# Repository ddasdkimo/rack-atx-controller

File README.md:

# Rack ATX Controller · B.2 / R.3

十台 Linux 主機共用一塊 POWER／RESET 遠端按鍵控制板。**100×110 mm、兩層的 R.3 佈線版已連通；中央板與轉接板 DRC／未連接均為 0。尚未製造放行。**

[公開佈局](https://rack-atx-controller-ddasdkimo.raidavid.chatgpt.site/layout.html) · [3D／兩台主機接線](https://rack-atx-controller-ddasdkimo.raidavid.chatgpt.site/) · [BOM](https://rack-atx-controller-ddasdkimo.raidavid.chatgpt.site/bom.html)

## 本版變更

- R.3 完成 USB 主對、Ethernet 終端集中、QFN 熱孔／鋼網窗，CC 電阻移近接頭。8 個 Ethernet 零件改為相同額定值的 0402；新增一個 Extended 料號，裝料費每單約多 US$3.07。原電路功能、接頭與 GPIO 不變。

- 移除全部 LED 偵測及十組隔離電源，保留二十個 TLP3122A 雙向隔離接點。原 POWER／RESET 按鈕經被動分接板並聯；原機殼 LED 直接留在主機板上。
- 原理圖／BOM 為 B.2；R.3 原生 PCB 有 300 個電氣元件、4 個固定孔、3,855 段走線與 252 個過孔。較 S.2 的 200×170 mm 面積減少約 68%。
- 修正模擬發現的計時與開機預設電位問題：MC14541B 計數式限時、1 nF C0G、獨立 ARM 閘控，GPIO 改為 4／6／7。
- 兩板 ERC／DRC／未連接均為 0。26×34 mm 被動轉接板為 6 個元件、30 段走線。16 組角落與 9 種狀態的 ngspice 行為模型通過，模型脈寬 11.26–21.46 秒。USB／Ethernet 的原生幾何與回流已由指定 CLI 獨立複查；兩層板沒有工廠控阻保證，尚未完成實板資格驗證，還需工廠 DFM 和實機驗證；目前已有 Gerber／鑽孔／BOM／CPL 審閱包，第二輪獨立離線加工檔複查沒有發現阻擋項；已取得五片完整報價；JLC 校正數值已通過獨立複查；TVS／網路座的供應商方向及 QFN 工藝仍待客服確認，尚未製造放行。

## 設計檔

- [B.2 KiCad 原理圖與 R.3 PCB](hardware/cad/B2/)
- [主控原理圖 PDF](hardware/release/controller-schematic.pdf)／[被動分接板 PDF](hardware/release/adapter-schematic.pdf)
- [硬體與接線](hardware/HARDWARE.md)／[佈局理由](hardware/LAYOUT-S3.md)／[R.3 佈線檢查與限制](hardware/ROUTING-R3.md)
- [BOM 與成本](hardware/bom/)／[費率假設](hardware/JLCPCB.md)
- [模擬方法與限制](hardware/simulation/README.md)／[B.2 結果](hardware/simulation/results/B2-summary.json)

J01–J10 是自訂 JST PHD 10 pin，**不是主機板通用 F_PANEL 或 Ethernet**。只接 pin 1/2 POWER、3/4 RESET、9 本機按鍵 ESD 參考地；5–8、10 不接。每台 HOST_REF 僅屬該台，與主控及其他主機保持隔離。線束與主機板跳線按實際手冊逐台核對。

## 成本範圍

2026-10-15 在登入 JLC 後取得五片正常 Economic 報價：**裸板 US$28.25、零件 US$168.86、組裝相關費 US$78.37，合計 US$275.48**，平均 US$55.10／片。板子＋零件為 US$197.11。採 ENIG 1µin／蓋油，一般交期、不加急；未含運稅、轉接板、線束、外殼與供電配件。QFN 工藝及 CPL 校正仍待確認，不代表已可生產。詳見 [實際報價](hardware/JLCPCB.md) 及 [加工檔審閱包](hardware/manufacturing/R3-candidate)。

## 重建

```sh
python3 scripts/build.py
python3 scripts/check.py
python3 -m http.server 8766 --directory dist
```

電路與原生 PCB 的完整重建方式見 [CAD 說明](hardware/cad/README.md)。3D 使用固定版本 Three.js，元件本體為簡化外形，但中央板與轉接板尺寸／位置／銅箔來自原生 KiCad；兩台主機為接線示意。網站沒有操作真實主機或上傳私密資訊的功能。

每次硬體變動須同步原理圖、BOM、3D、接線圖與公開網頁，見 [AGENTS.md](AGENTS.md)。B.1／S.2／R.0／R.1 資料與本機走線檢查點保留為歷史，不能繼續當作現行電路。

送件進度與證據見 [檢查清單](hardware/RELEASE-CHECKLIST.md)。客服問題結案後固定最終送樣包，再請同一位 `rack-atx-controller` 複查。

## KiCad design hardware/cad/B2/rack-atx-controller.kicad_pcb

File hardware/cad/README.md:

# Active CAD: B.2 schematic / R.2 routing

Open `B2/rack-atx-controller.kicad_pro` for the controller schematic; `B2/adapter.kicad_pro` for the six-component passive adapter; `B2/rack-atx-controller.kicad_pcb` in PCB Editor for the 100×110 mm routed candidate. Routing was authorized by the user. No Gerber or CPL exists.

The B.2 controller contains 300 electrical components; the placement adds four M3 holes. The controller has 2,754 track segments and 185 vias; the 26×34 mm adapter has 30 segments and no vias. Both boards have zero native unconnected items and configured DRC violations. The web 3D uses native placement, copper and adapter coordinates with simplified component envelopes. USB/Ethernet qualification, factory DFM and physical tests remain; see ../ROUTING-R2.md. Generators write into B2/placement to preserve the routed master.

```sh
python3 scripts/make-schematic.py
kicad-cli sch export netlist --format kicadxml -o artifacts/local/controller.xml hardware/cad/B2/rack-atx-controller.kicad_sch
kicad-cli sch export netlist --format kicadxml -o artifacts/local/adapter.xml hardware/cad/B2/adapter.kicad_sch
kicad-cli sch erc --format json -o artifacts/local/erc.json hardware/cad/B2/rack-atx-controller.kicad_sch
kicad-cli sch erc --format json -o artifacts/local/adapter-erc.json hardware/cad/B2/adapter.kicad_sch
python3 scripts/check-circuit.py
python3 hardware/simulation/run-b2.py
python3 scripts/cost.py
kicad-cli sch export pdf -o hardware/release/controller-schematic.pdf hardware/cad/B2/rack-atx-controller.kicad_sch
kicad-cli sch export pdf -o hardware/release/adapter-schematic.pdf hardware/cad/B2/adapter.kicad_sch
```

Run from the repository root. Use KiCad's bundled Python (wx + pcbnew) for `scripts/make-layout-s3.py` and `scripts/check-layout-s3.py`, then `kicad-cli pcb drc --format json -o artifacts/local/s3-drc.json hardware/cad/B2/rack-atx-controller.kicad_pcb`. Export/ ERC operations on the same project must run sequentially. Source library paths in generators currently target macOS KiCad; adapt paths on other platforms.

BOM, schematic and PCB candidate footprints agree; custom TLP3122A and input-terminal land patterns live in `RackATX.pretty`, referenced relative to B2. Manufacturer/physical DFM qualification is still required. Raw CLI netlists stay ignored because they include workstation paths. Never publish them. Historical CAD in this directory and archive/B1 is retained, not the current revision.

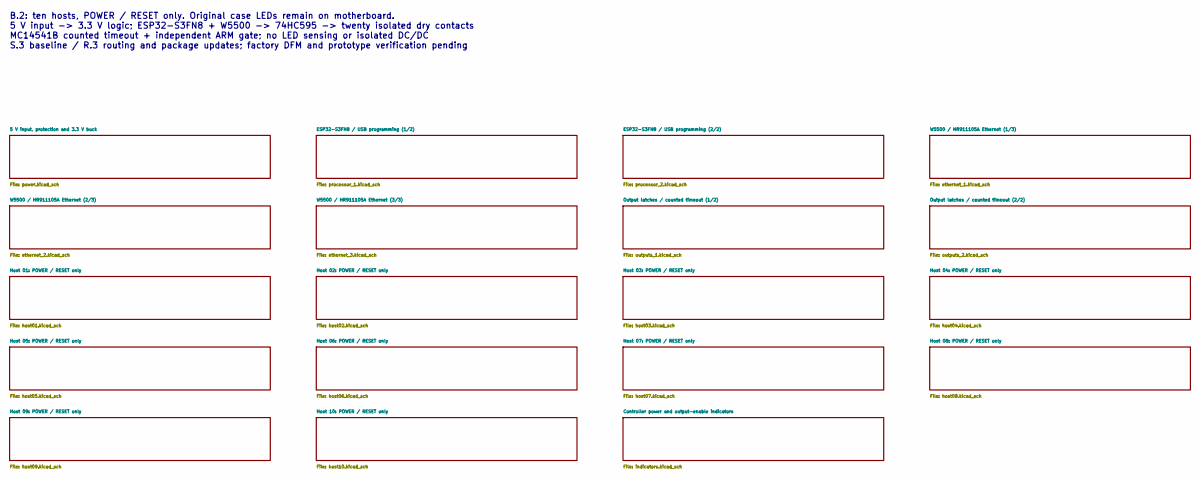
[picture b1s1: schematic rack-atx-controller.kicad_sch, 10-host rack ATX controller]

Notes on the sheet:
B.2: ten hosts, POWER / RESET only. Original case LEDs remain on motherboard. 5 V input -> 3.3 V logic; ESP32-S3FN8 + W5500 -> 74HC595 -> twenty isolated dry contacts MC14541B counted timeout + independent ARM gate; no LED sensing or isolated DC/DC S.3 baseline / R.3 routing and package updates; fa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

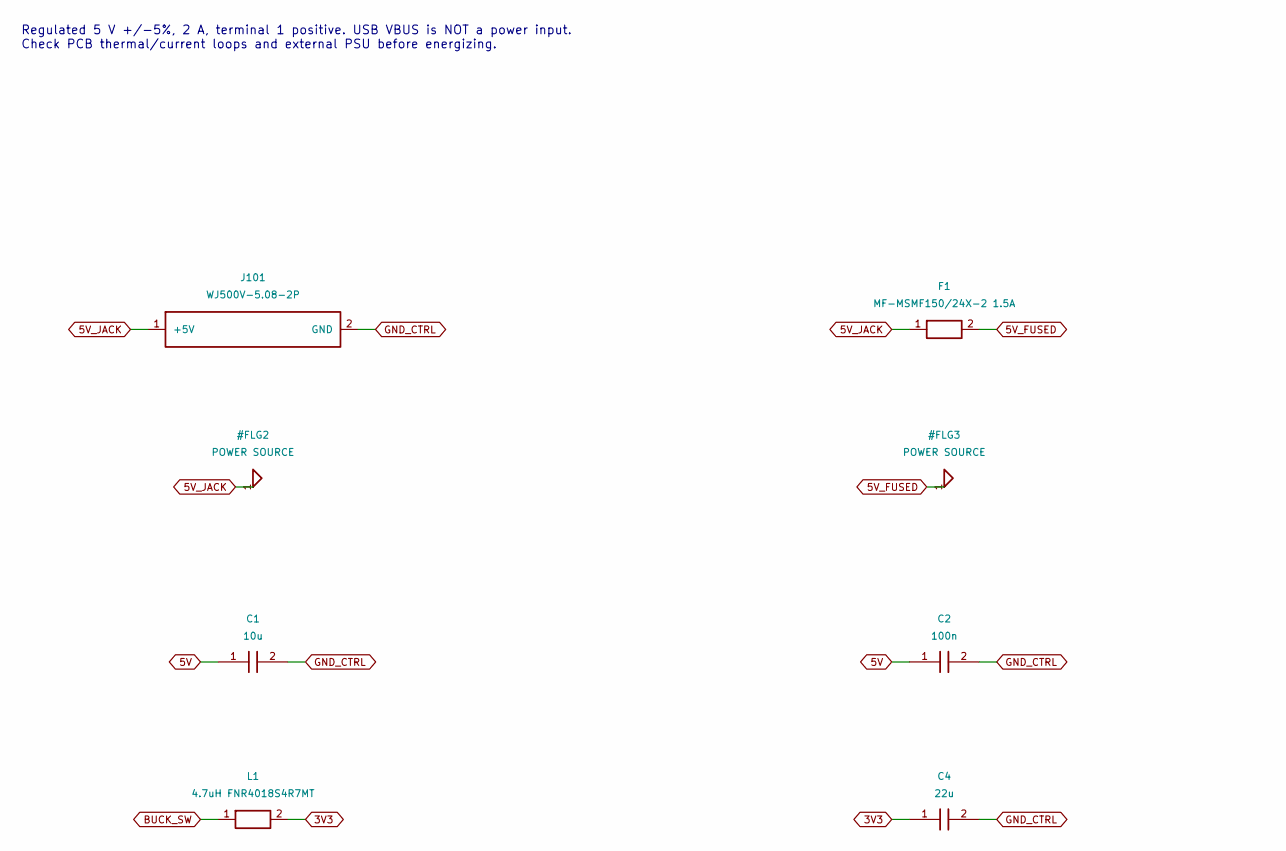
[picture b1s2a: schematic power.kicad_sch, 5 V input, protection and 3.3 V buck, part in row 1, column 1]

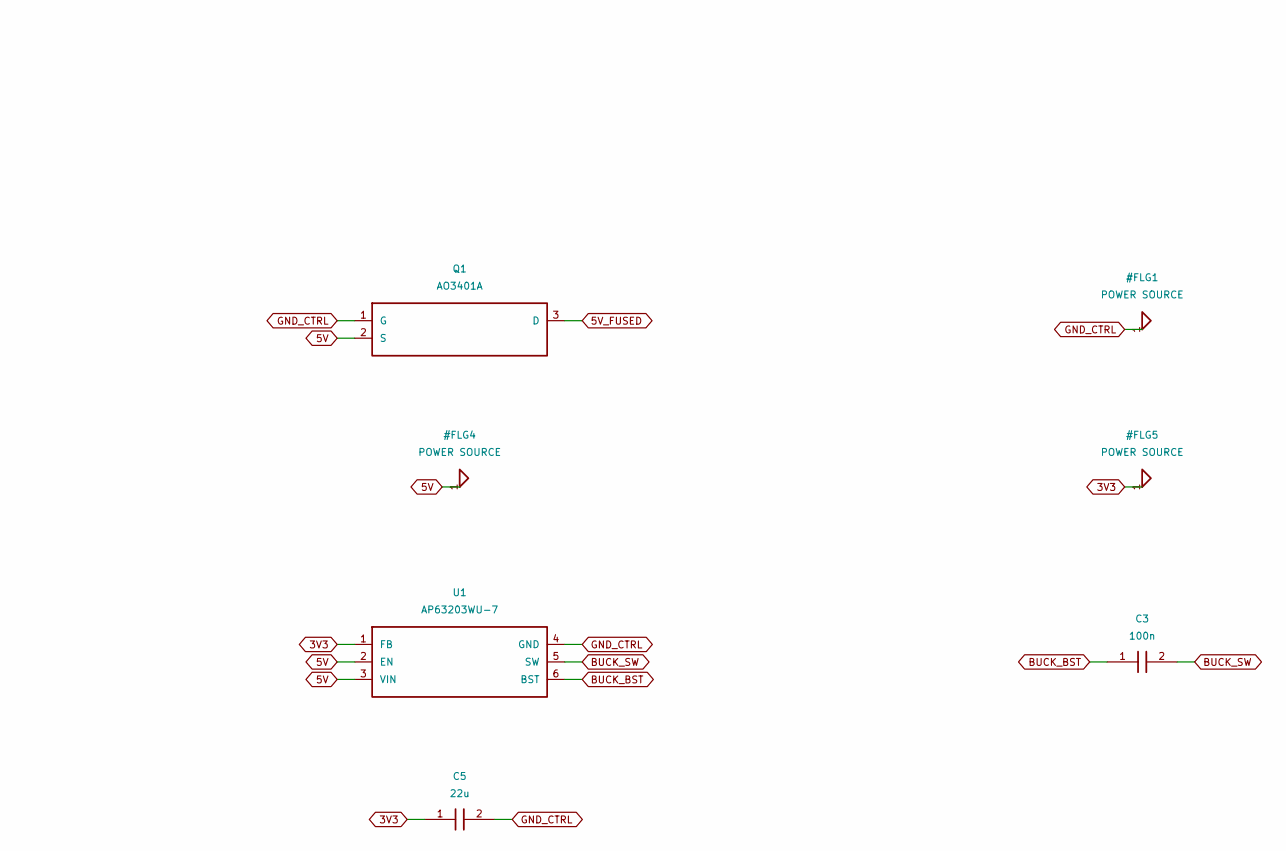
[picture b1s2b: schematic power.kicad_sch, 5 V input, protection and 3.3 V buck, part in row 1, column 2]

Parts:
C1: 10u; C_0805_2012Metric; MPN CL21A106KAYNNNE; LCSC C15850
C2, C3: 100n; C_0603_1608Metric; MPN CC0603KRX7R9BB104; LCSC C14663
C4, C5: 22u; C_0805_2012Metric; MPN CL21A226MAQNNNE; LCSC C45783
F1: MF-MSMF150/24X-2 1.5A; Fuse_1812_4532Metric; MPN MF-MSMF150/24X-2; LCSC C78695
J101: WJ500V-5.08-2P; WJ500V_5.08_2P; MPN WJ500V-5.08-2P; LCSC C8465
L1: 4.7uH FNR4018S4R7MT; L_Changjiang_FNR4018S; MPN FNR4018S4R7MT; LCSC C167806
Q1: AO3401A; SOT-23; MPN AO3401A; LCSC C15127
U1: AP63203WU-7; TSOT-23-6; MPN AP63203WU-7; LCSC C780769

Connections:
3V3: C4.1, C5.1, L1.2, U1.1 (FB); also elsewhere on the board
5V: C1.1, C2.1, Q1.2 (S), U1.2 (EN), U1.3 (VIN); also elsewhere on the board
5V_FUSED: F1.2, Q1.3 (D)
5V_JACK: F1.1, J101.1 (+5V)
BUCK_BST: C3.1, U1.6 (BST)
BUCK_SW: C3.2, L1.1, U1.5 (SW)
GND_CTRL: C1.2, C2.2, C4.2, C5.2, J101.2 (GND), Q1.1 (G), U1.4 (GND); also elsewhere on the board

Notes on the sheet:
Regulated 5 V +/-5%, 2 A, terminal 1 positive. USB VBUS is NOT a power input. Check PCB thermal/current loops and external PSU before energizing.

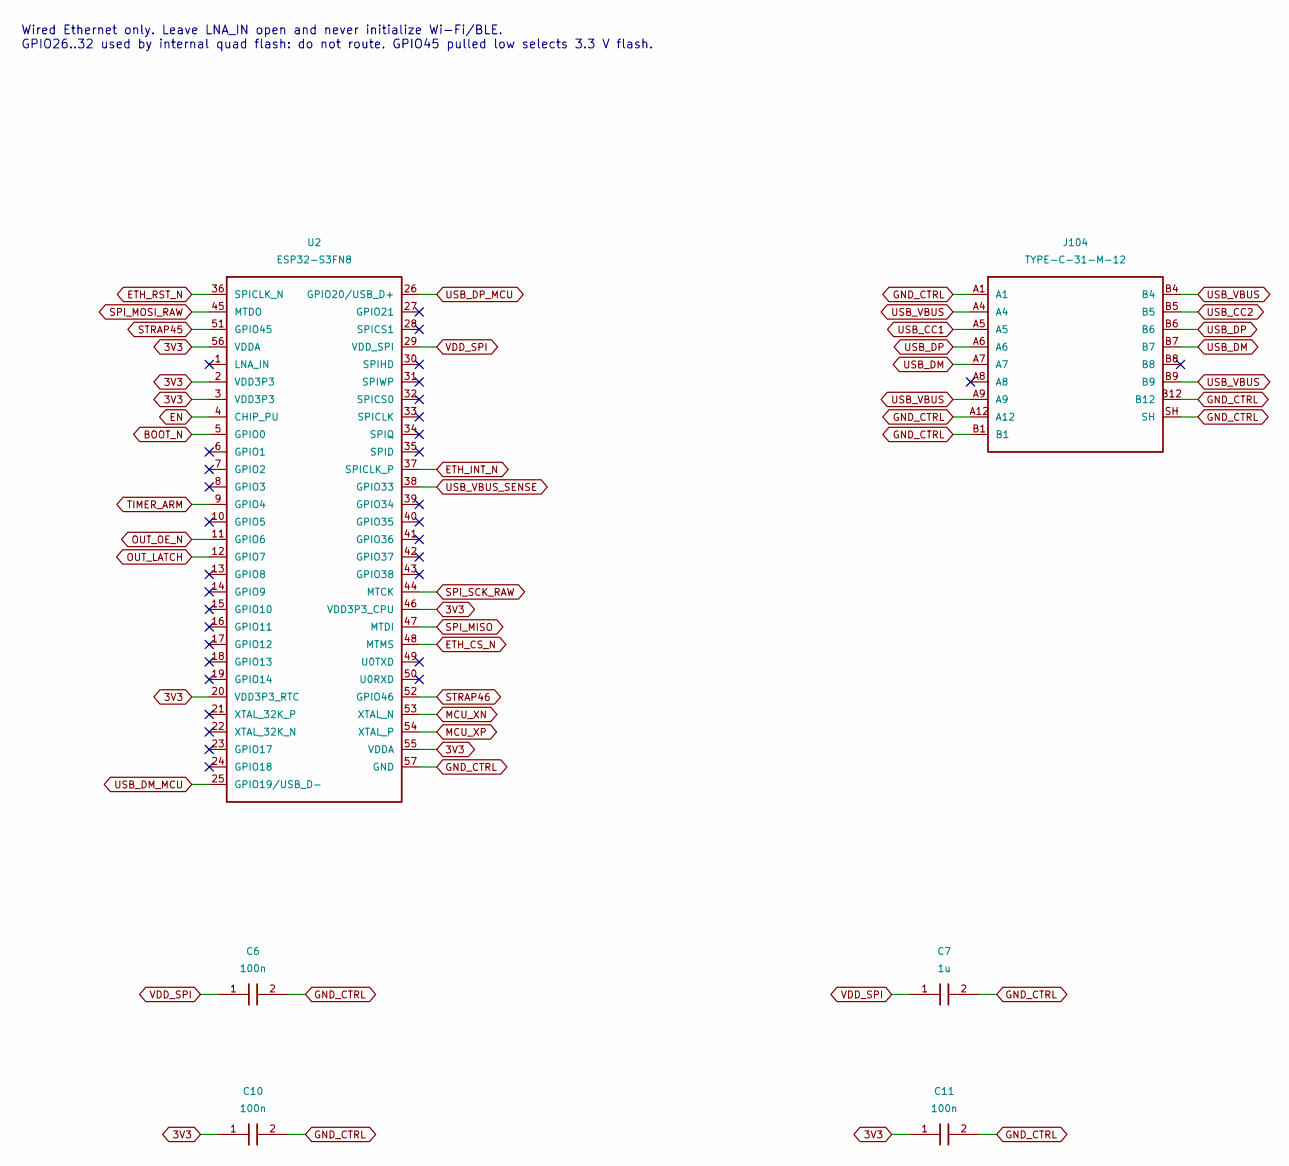
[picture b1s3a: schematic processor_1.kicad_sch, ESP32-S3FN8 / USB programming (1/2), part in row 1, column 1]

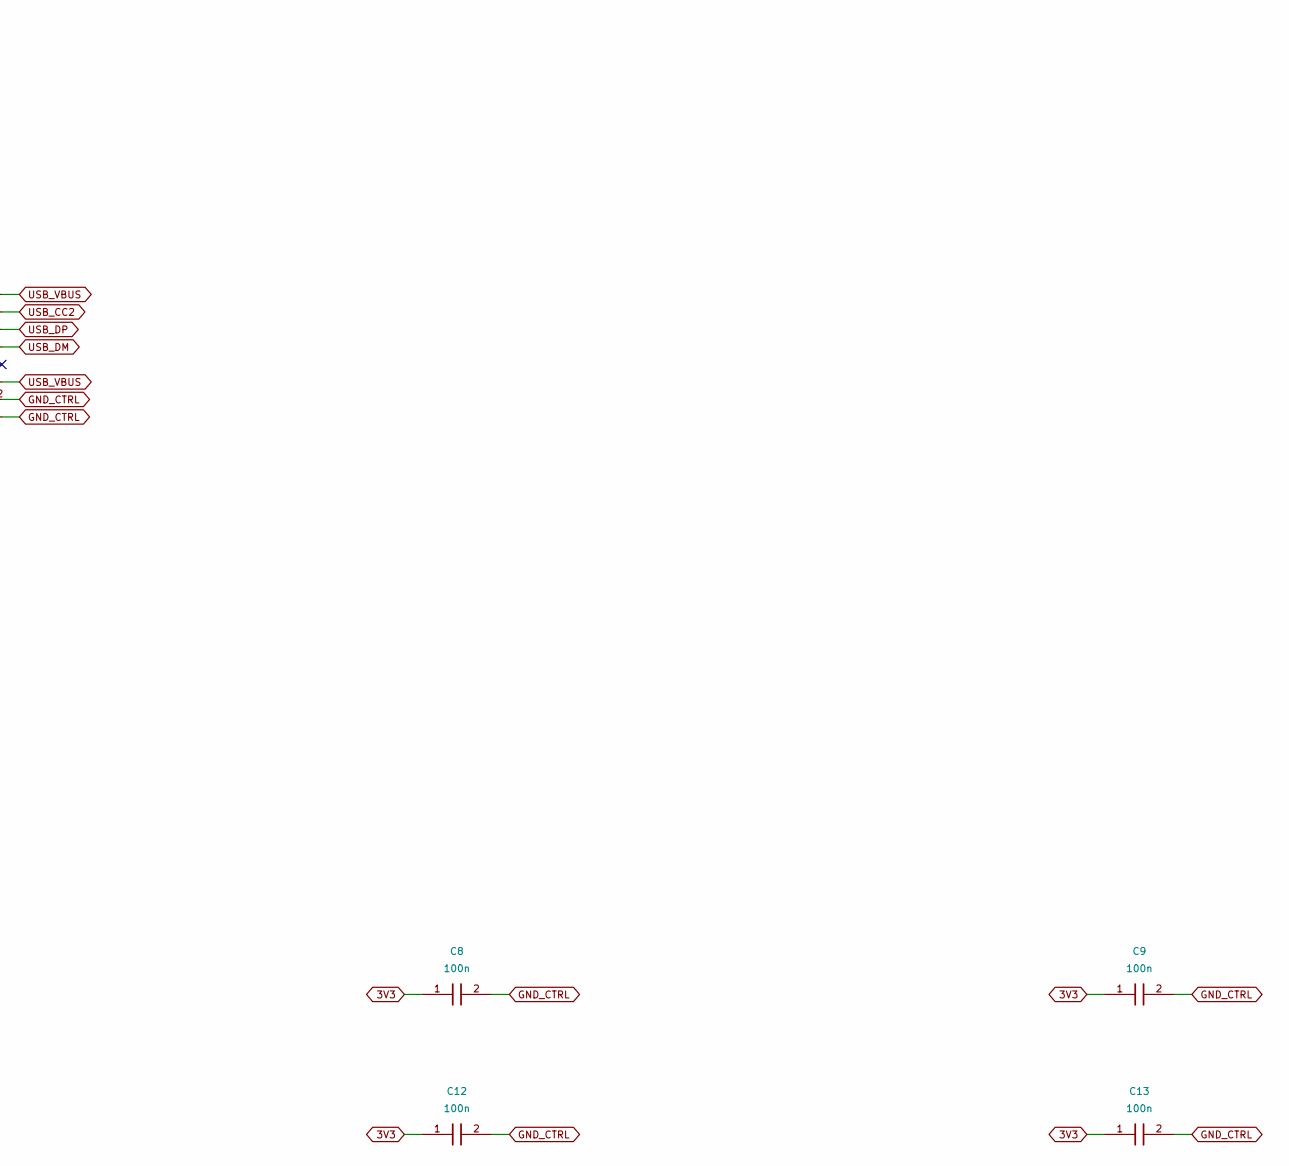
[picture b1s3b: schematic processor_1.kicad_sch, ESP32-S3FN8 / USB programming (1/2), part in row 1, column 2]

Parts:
C6, C8, C9, C10, C11, C12, C13: 100n; C_0603_1608Metric; MPN CC0603KRX7R9BB104; LCSC C14663
C7: 1u; C_0603_1608Metric; MPN CL10A105KB8NNNC; LCSC C15849
J104: TYPE-C-31-M-12; USB_C_Receptacle_HRO_TYPE-C-31-M-12; MPN TYPE-C-31-M-12; LCSC C165948
U2: ESP32-S3FN8; ESP32_S3_QFN56_EP4_16Window; MPN ESP32-S3FN8; LCSC C2913196

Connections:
3V3: C8.1, C9.1, C10.1, C11.1, C12.1, C13.1, U2.2 (VDD3P3), U2.3 (VDD3P3), U2.20 (VDD3P3_RTC), U2.46 (VDD3P3_CPU), U2.55 (VDDA), U2.56 (VDDA); also elsewhere on the board
BOOT_N: U2.5 (GPIO0); also elsewhere on the board
EN: U2.4 (CHIP_PU); also elsewhere on the board
ETH_CS_N: U2.48 (MTMS); also elsewhere on the board
ETH_INT_N: U2.37 (SPICLK_P); also elsewhere on the board
ETH_RST_N: U2.36 (SPICLK_N); also elsewhere on the board
GND_CTRL: C6.2, C7.2, C8.2, C9.2, C10.2, C11.2, C12.2, C13.2, J104.A1, J104.A12, J104.B1, J104.B12, J104.SH, U2.57 (GND); also elsewhere on the board
MCU_XN: U2.53 (XTAL_N); also elsewhere on the board
MCU_XP: U2.54 (XTAL_P); also elsewhere on the board
OUT_LATCH: U2.12 (GPIO7); also elsewhere on the board
OUT_OE_N: U2.11 (GPIO6); also elsewhere on the board
SPI_MISO: U2.47 (MTDI); also elsewhere on the board
SPI_MOSI_RAW: U2.45 (MTDO); also elsewhere on the board
SPI_SCK_RAW: U2.44 (MTCK); also elsewhere on the board
STRAP45: U2.51 (GPIO45); also elsewhere on the board
STRAP46: U2.52 (GPIO46); also elsewhere on the board
TIMER_ARM: U2.9 (GPIO4); also elsewhere on the board
USB_CC1: J104.A5; also elsewhere on the board
USB_CC2: J104.B5; also elsewhere on the board
USB_DM: J104.A7, J104.B7; also elsewhere on the board
USB_DM_MCU: U2.25 (GPIO19/USB_D-); also elsewhere on the board
USB_DP: J104.A6, J104.B6; also elsewhere on the board
USB_DP_MCU: U2.26 (GPIO20/USB_D+); also elsewhere on the board
USB_VBUS: J104.A4, J104.A9, J104.B4, J104.B9; also elsewhere on the board
USB_VBUS_SENSE: U2.38 (GPIO33); also elsewhere on the board
VDD_SPI: C6.1, C7.1, U2.29 (VDD_SPI)

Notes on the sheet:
Wired Ethernet only. Leave LNA_IN open and never initialize Wi-Fi/BLE. GPIO26..32 used by internal quad flash: do not route. GPIO45 pulled low selects 3.3 V flash.

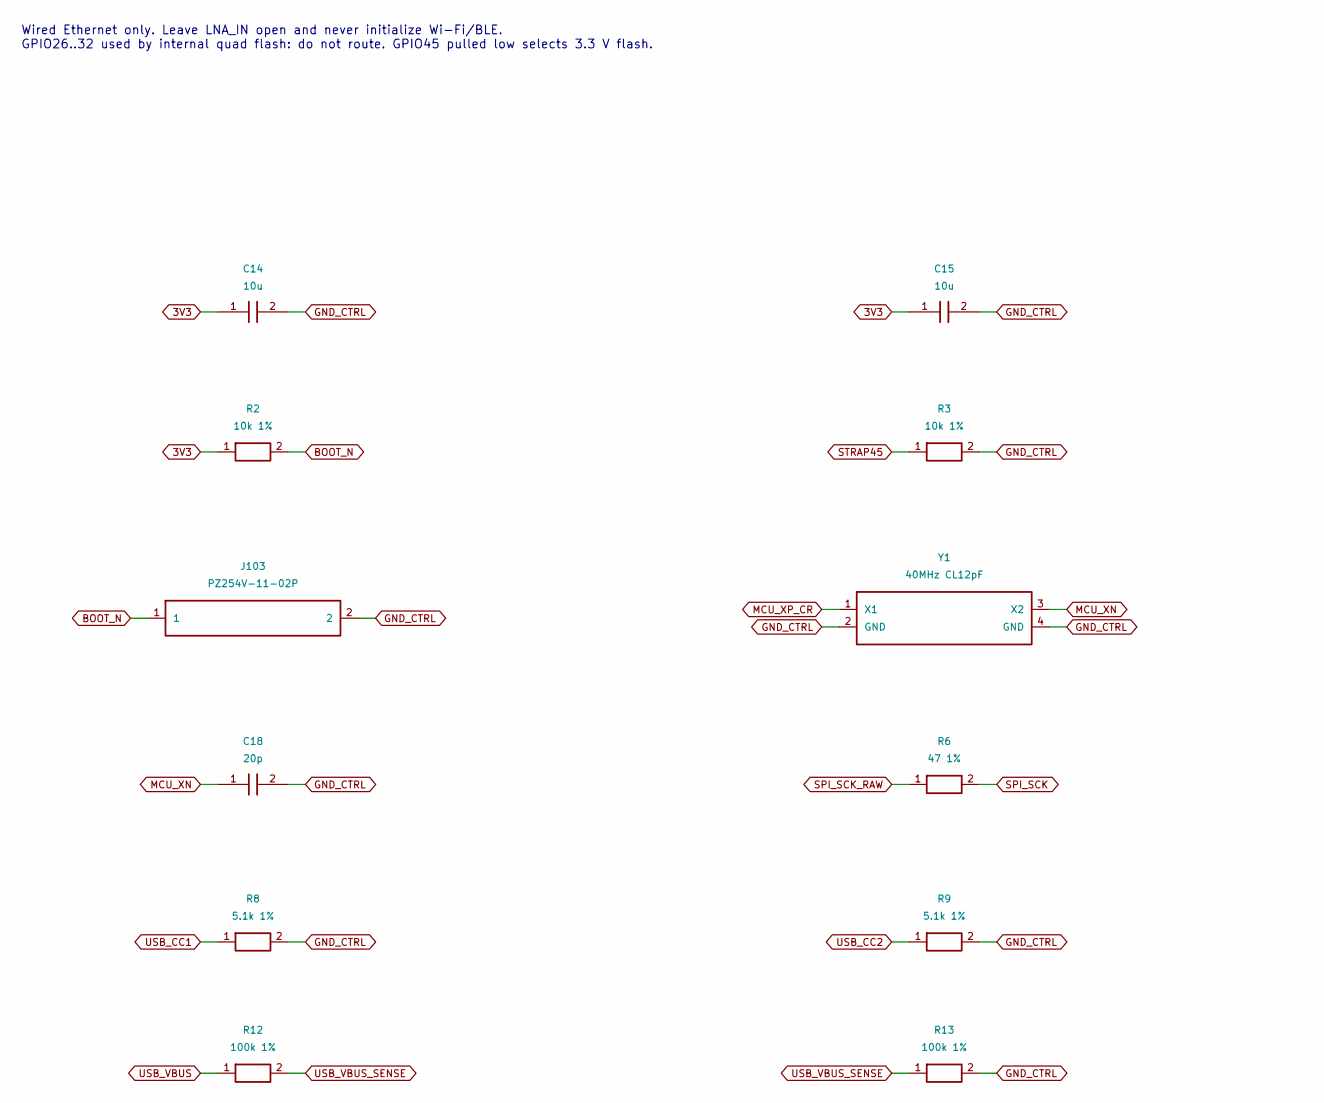
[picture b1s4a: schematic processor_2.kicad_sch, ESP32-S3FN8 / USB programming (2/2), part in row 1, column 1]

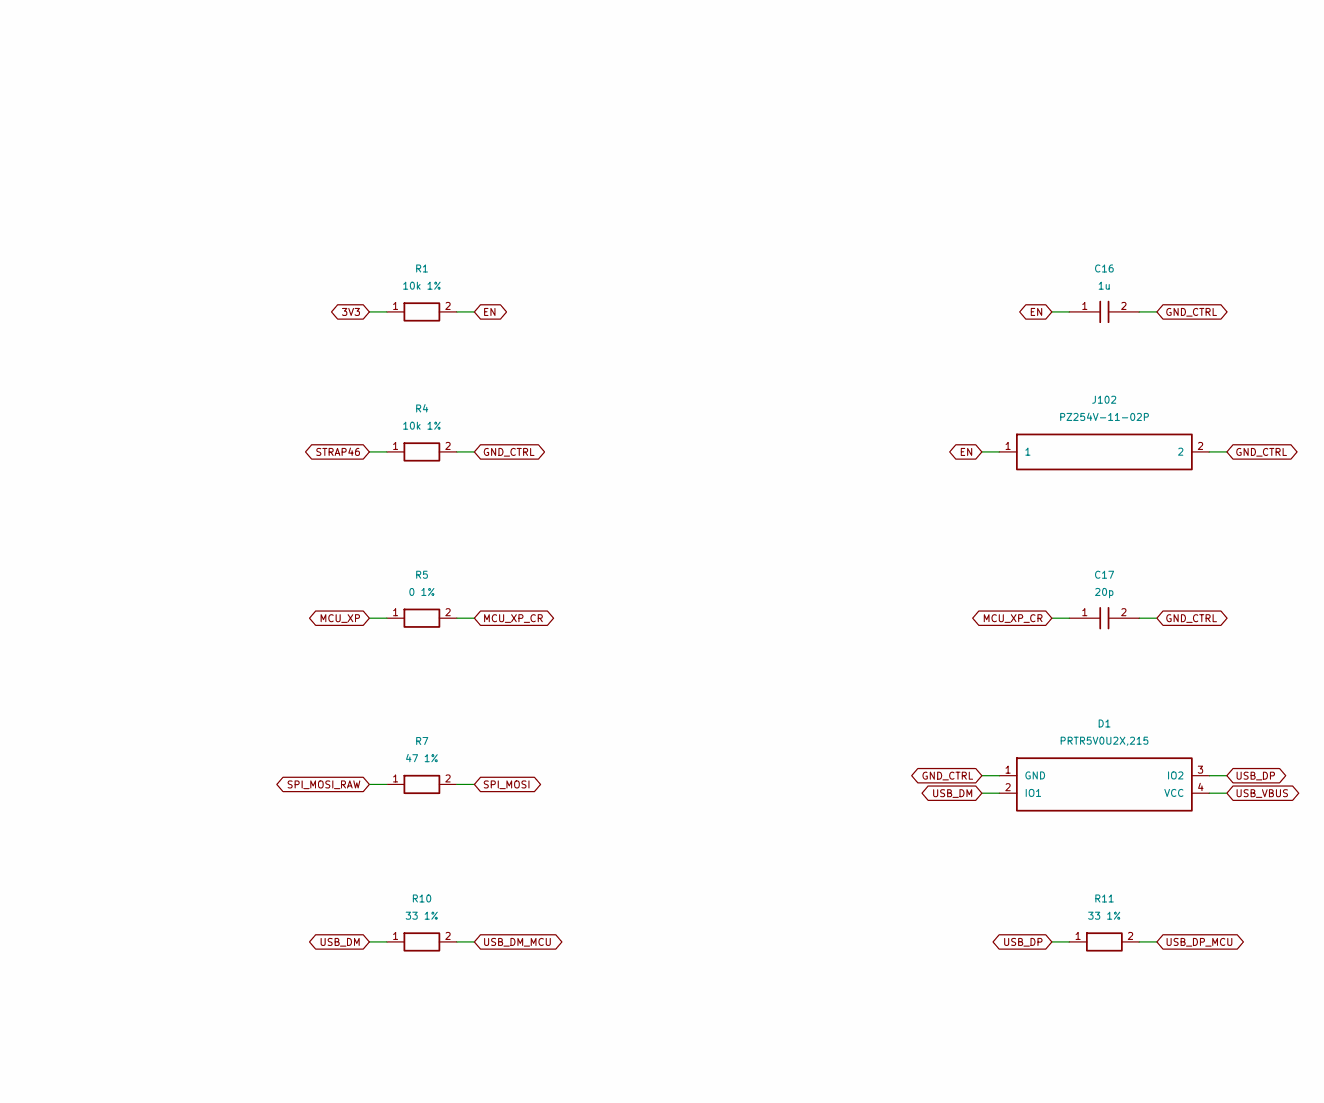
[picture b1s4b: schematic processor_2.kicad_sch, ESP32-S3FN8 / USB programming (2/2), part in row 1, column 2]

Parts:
C14, C15: 10u; C_0805_2012Metric; MPN CL21A106KAYNNNE; LCSC C15850
C16: 1u; C_0603_1608Metric; MPN CL10A105KB8NNNC; LCSC C15849
C17, C18: 20p; C_0603_1608Metric; MPN CL10C200JB8NNNC; LCSC C1648
D1: PRTR5V0U2X,215; SOT-143; MPN PRTR5V0U2X,215; LCSC C12333
J102, J103: PZ254V-11-02P; PinHeader_1x02_P2.54mm_Vertical; MPN PZ254V-11-02P; LCSC C492401
R1, R2, R3, R4: 10k 1%; R_0603_1608Metric; MPN 0603WAF1002T5E; LCSC C25804
R5: 0 1%; R_0603_1608Metric; MPN 0603WAF0000T5E; LCSC C21189
R6, R7: 47 1%; R_0603_1608Metric; MPN 0603WAF470JT5E; LCSC C23182
R8, R9: 5.1k 1%; R_0603_1608Metric; MPN 0603WAF5101T5E; LCSC C23186
R10, R11: 33 1%; R_0603_1608Metric; MPN 0603WAF330JT5E; LCSC C23140
R12, R13: 100k 1%; R_0603_1608Metric; MPN 0603WAF1003T5E; LCSC C25803
Y1: 40MHz CL12pF; Crystal_SMD_3225-4Pin_3.2x2.5mm; MPN XL2EL89COI-111YLC-40M; LCSC C18214314

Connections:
3V3: C14.1, C15.1, R1.1, R2.1; also elsewhere on the board
BOOT_N: J103.1, R2.2; also elsewhere on the board
EN: C16.1, J102.1, R1.2; also elsewhere on the board
GND_CTRL: C14.2, C15.2, C16.2, C17.2, C18.2, D1.1 (GND), J102.2, J103.2, R3.2, R4.2, R8.2, R9.2, R13.2, Y1.2 (GND), Y1.4 (GND); also elsewhere on the board
MCU_XN: C18.1, Y1.3 (X2); also elsewhere on the board
MCU_XP: R5.1; also elsewhere on the board
MCU_XP_CR: C17.1, R5.2, Y1.1 (X1)
SPI_MOSI: R7.2; also elsewhere on the board
SPI_MOSI_RAW: R7.1; also elsewhere on the board
SPI_SCK: R6.2; also elsewhere on the board
SPI_SCK_RAW: R6.1; also elsewhere on the board
STRAP45: R3.1; also elsewhere on the board
STRAP46: R4.1; also elsewhere on the board
USB_CC1: R8.1; also elsewhere on the board
USB_CC2: R9.1; also elsewhere on the board
USB_DM: D1.2 (IO1), R10.1; also elsewhere on the board
USB_DM_MCU: R10.2; also elsewhere on the board
USB_DP: D1.3 (IO2), R11.1; also elsewhere on the board
USB_DP_MCU: R11.2; also elsewhere on the board
USB_VBUS: D1.4 (VCC), R12.1; also elsewhere on the board
USB_VBUS_SENSE: R12.2, R13.1; also elsewhere on the board

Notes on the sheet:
Wired Ethernet only. Leave LNA_IN open and never initialize Wi-Fi/BLE. GPIO26..32 used by internal quad flash: do not route. GPIO45 pulled low selects 3.3 V flash.

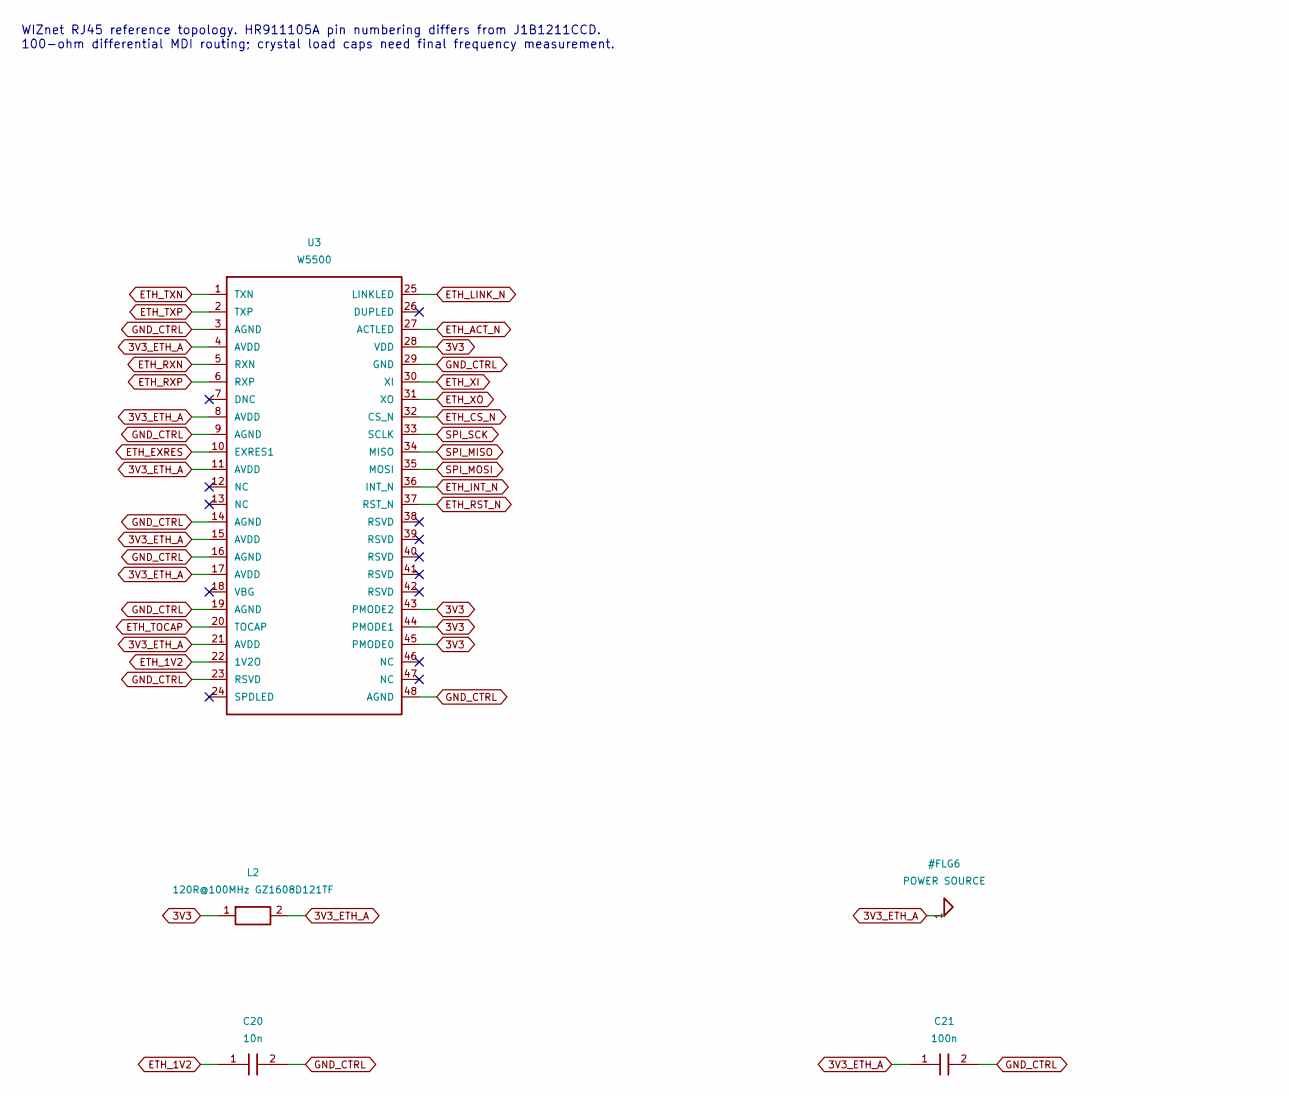
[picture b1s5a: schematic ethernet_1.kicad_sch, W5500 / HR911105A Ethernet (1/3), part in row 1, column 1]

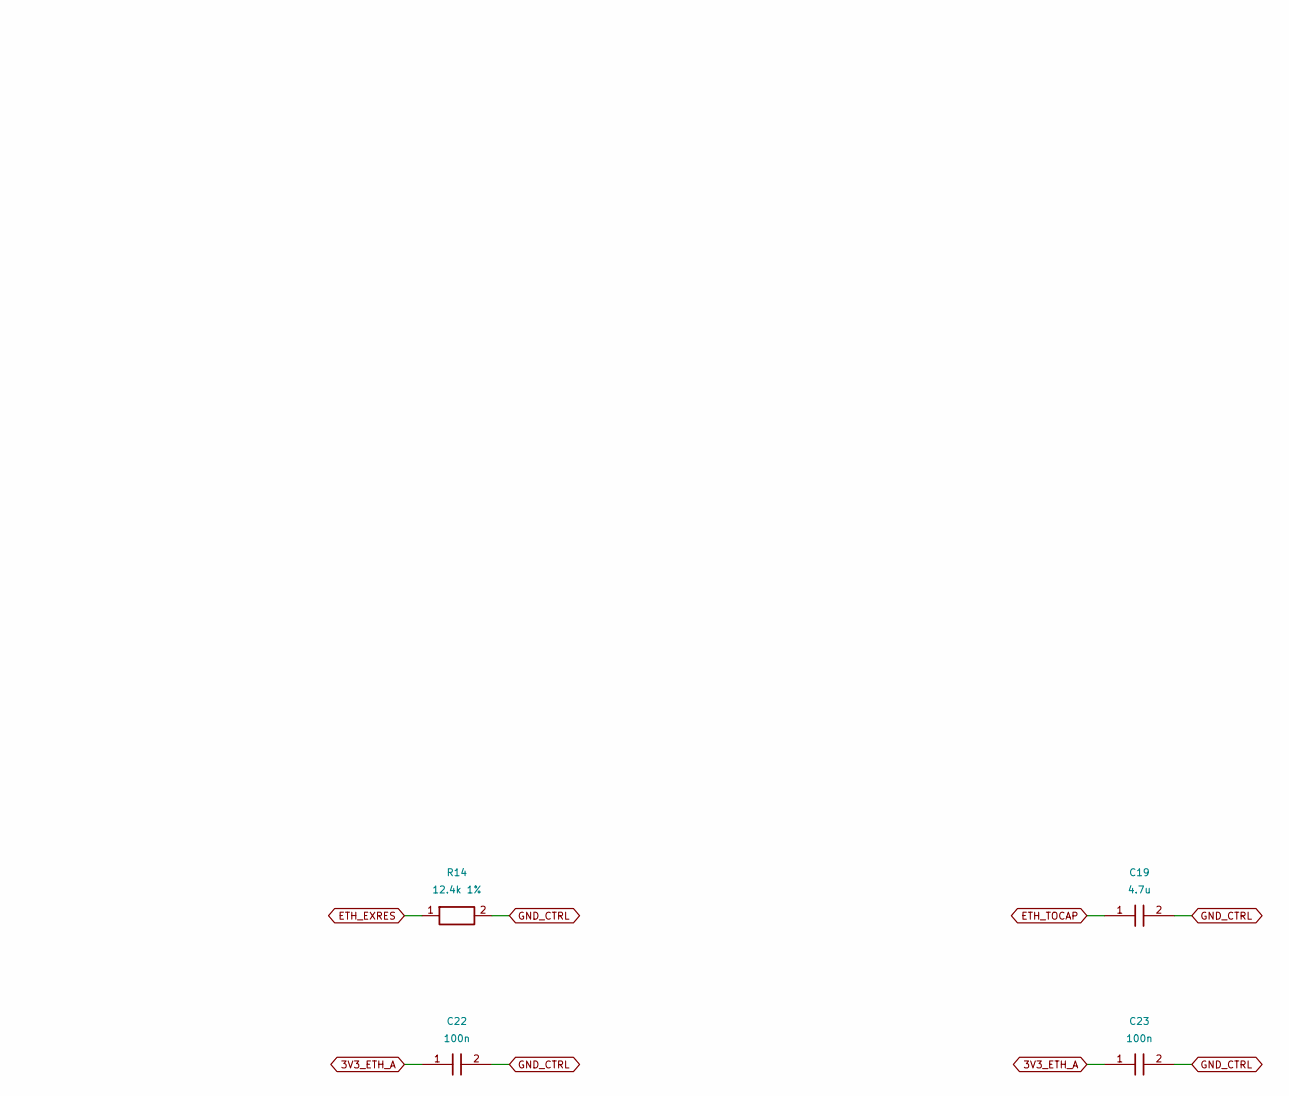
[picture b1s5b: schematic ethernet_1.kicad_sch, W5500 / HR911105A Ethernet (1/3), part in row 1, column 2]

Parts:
C19: 4.7u; C_0603_1608Metric; MPN CL10A475KO8NNNC; LCSC C19666
C20: 10n; C_0603_1608Metric; MPN 0603B103K500NT; LCSC C57112
C21, C22, C23: 100n; C_0402_1005Metric; MPN CL05B104KO5NNNC; LCSC C1525
L2: 120R@100MHz GZ1608D121TF; L_0603_1608Metric; MPN GZ1608D121TF; LCSC C12391
R14: 12.4k 1%; R_0603_1608Metric; MPN 0603WAF1242T5E; LCSC C22865
U3: W5500; LQFP-48_7x7mm_P0.5mm; MPN W5500; LCSC C32843

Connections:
3V3: L2.1, U3.28 (VDD), U3.43 (PMODE2), U3.44 (PMODE1), U3.45 (PMODE0); also elsewhere on the board
3V3_ETH_A: C21.1, C22.1, C23.1, L2.2, U3.4 (AVDD), U3.8 (AVDD), U3.11 (AVDD), U3.15 (AVDD), U3.17 (AVDD), U3.21 (AVDD); also elsewhere on the board
ETH_1V2: C20.1, U3.22 (1V2O)
ETH_ACT_N: U3.27 (ACTLED); also elsewhere on the board
ETH_CS_N: U3.32 (CS_N); also elsewhere on the board
ETH_EXRES: R14.1, U3.10 (EXRES1)
ETH_INT_N: U3.36 (INT_N); also elsewhere on the board
ETH_LINK_N: U3.25 (LINKLED); also elsewhere on the board
ETH_RST_N: U3.37 (RST_N); also elsewhere on the board
ETH_RXN: U3.5 (RXN); also elsewhere on the board
ETH_RXP: U3.6 (RXP); also elsewhere on the board
ETH_TOCAP: C19.1, U3.20 (TOCAP)
ETH_TXN: U3.1 (TXN); also elsewhere on the board
ETH_TXP: U3.2 (TXP); also elsewhere on the board
ETH_XI: U3.30 (XI); also elsewhere on the board
ETH_XO: U3.31 (XO); also elsewhere on the board
GND_CTRL: C19.2, C20.2, C21.2, C22.2, C23.2, R14.2, U3.3 (AGND), U3.9 (AGND), U3.14 (AGND), U3.16 (AGND), U3.19 (AGND), U3.23 (RSVD), U3.29 (GND), U3.48 (AGND); also elsewhere on the board
SPI_MISO: U3.34 (MISO); also elsewhere on the board
SPI_MOSI: U3.35 (MOSI); also elsewhere on the board
SPI_SCK: U3.33 (SCLK); also elsewhere on the board

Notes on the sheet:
WIZnet RJ45 reference topology. HR911105A pin numbering differs from J1B1211CCD. 100-ohm differential MDI routing; crystal load caps need final frequency measurement.

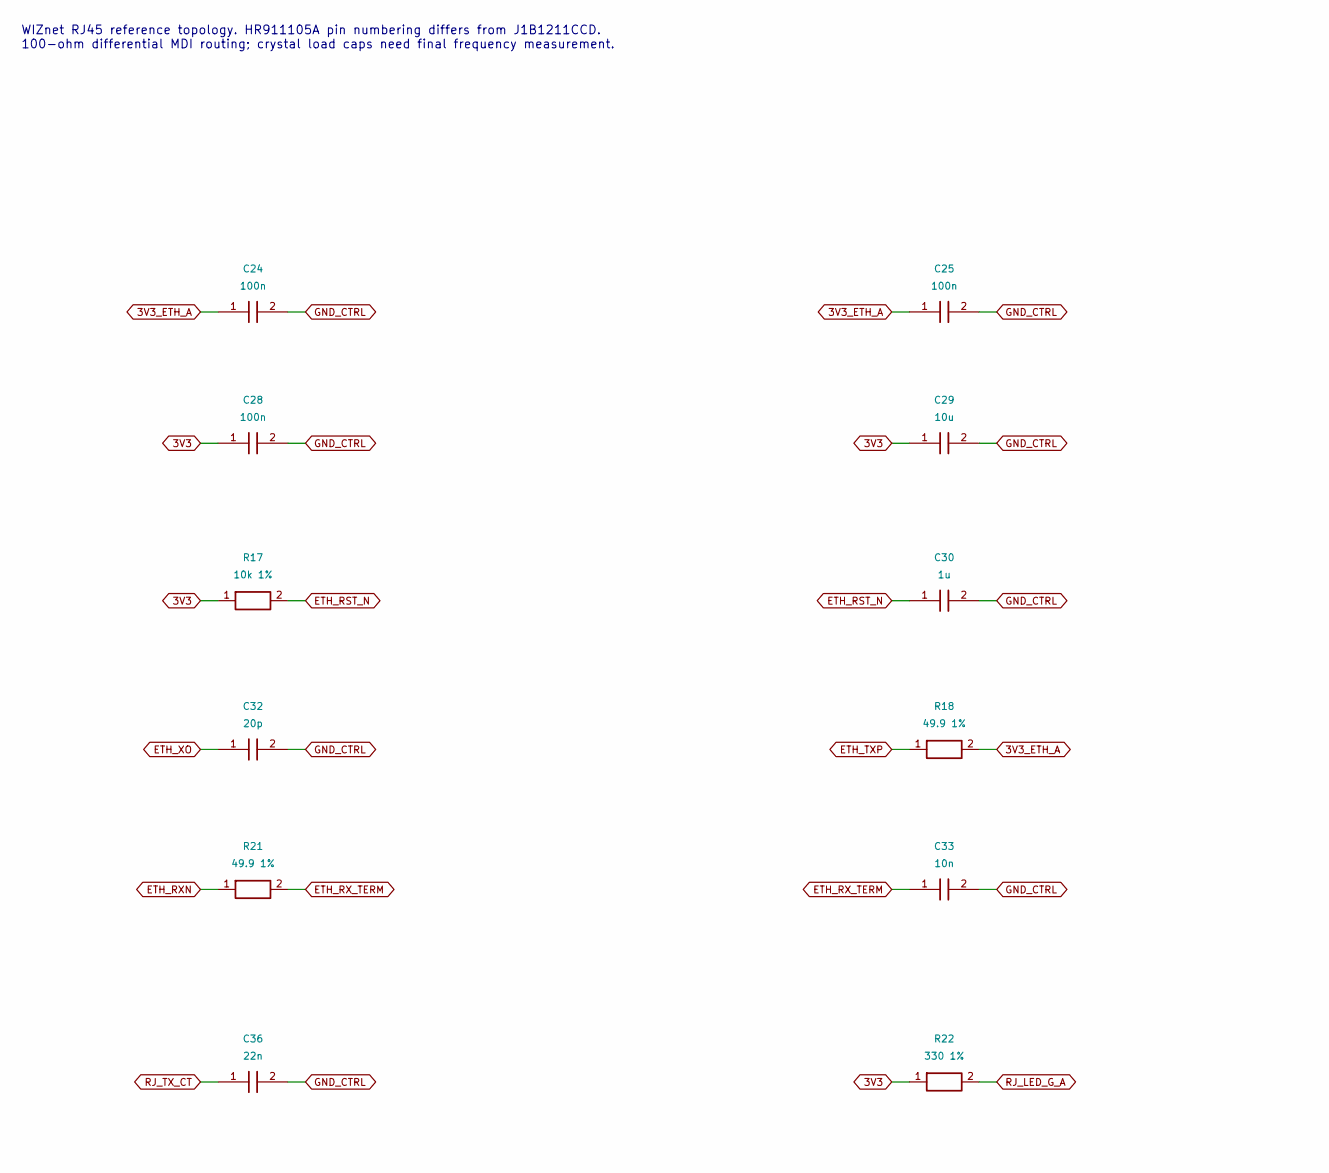
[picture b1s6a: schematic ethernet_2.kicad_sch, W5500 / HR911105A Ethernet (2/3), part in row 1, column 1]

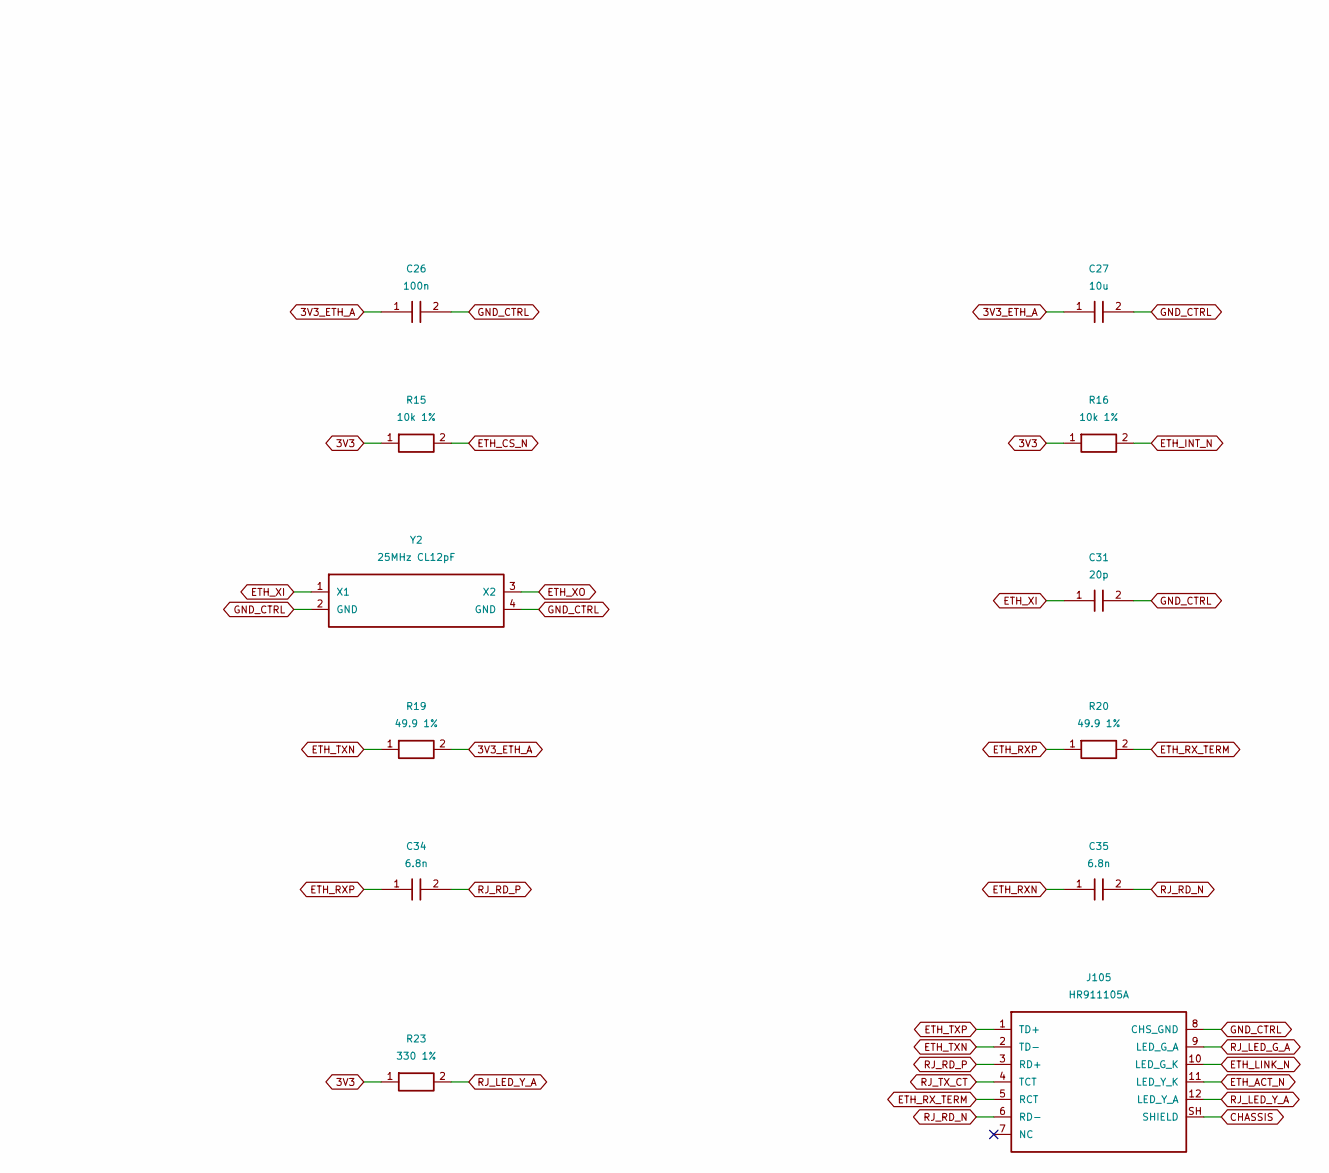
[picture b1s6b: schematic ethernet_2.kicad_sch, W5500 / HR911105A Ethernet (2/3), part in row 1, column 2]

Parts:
C24, C25, C26, C28: 100n; C_0603_1608Metric; MPN CC0603KRX7R9BB104; LCSC C14663
C27, C29: 10u; C_0805_2012Metric; MPN CL21A106KAYNNNE; LCSC C15850
C30: 1u; C_0603_1608Metric; MPN CL10A105KB8NNNC; LCSC C15849
C31, C32: 20p; C_0603_1608Metric; MPN CL10C200JB8NNNC; LCSC C1648
C33: 10n; C_0402_1005Metric; MPN CL05B103KB5NNNC; LCSC C15195
C34, C35: 6.8n; C_0402_1005Metric; MPN CL05B682KB5NNNC; LCSC C318580
C36: 22n; C_0805_2012Metric; MPN CL21B223KBANNNC; LCSC C1729
J105: HR911105A; RJ45_Hanrun_HR911105A_Horizontal; MPN HR911105A; LCSC C12074
R15, R16, R17: 10k 1%; R_0603_1608Metric; MPN 0603WAF1002T5E; LCSC C25804
R18, R19: 49.9 1%; R_0603_1608Metric; MPN 0603WAF499JT5E; LCSC C23185
R20, R21: 49.9 1%; R_0402_1005Metric; MPN 0402WGF499JTCE; LCSC C25120
R22, R23: 330 1%; R_0603_1608Metric; MPN 0603WAF3300T5E; LCSC C23138
Y2: 25MHz CL12pF; Crystal_SMD_3225-4Pin_3.2x2.5mm; MPN X322525MOB4SI; LCSC C9006

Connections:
3V3: C28.1, C29.1, R15.1, R16.1, R17.1, R22.1, R23.1; also elsewhere on the board
3V3_ETH_A: C24.1, C25.1, C26.1, C27.1, R18.2, R19.2; also elsewhere on the board
CHASSIS: J105.SH (SHIELD); also elsewhere on the board
ETH_ACT_N: J105.11 (LED_Y_K); also elsewhere on the board
ETH_CS_N: R15.2; also elsewhere on the board
ETH_INT_N: R16.2; also elsewhere on the board
ETH_LINK_N: J105.10 (LED_G_K); also elsewhere on the board
ETH_RST_N: C30.1, R17.2; also elsewhere on the board
ETH_RXN: C35.1, R21.1; also elsewhere on the board
ETH_RXP: C34.1, R20.1; also elsewhere on the board
ETH_RX_TERM: C33.1, J105.5 (RCT), R20.2, R21.2
ETH_TXN: J105.2 (TD-), R19.1; also elsewhere on the board
ETH_TXP: J105.1 (TD+), R18.1; also elsewhere on the board
ETH_XI: C31.1, Y2.1 (X1); also elsewhere on the board
ETH_XO: C32.1, Y2.3 (X2); also elsewhere on the board
GND_CTRL: C24.2, C25.2, C26.2, C27.2, C28.2, C29.2, C30.2, C31.2, C32.2, C33.2, C36.2, J105.8 (CHS_GND), Y2.2 (GND), Y2.4 (GND); also elsewhere on the board
RJ_LED_G_A: J105.9 (LED_G_A), R22.2
RJ_LED_Y_A: J105.12 (LED_Y_A), R23.2
RJ_RD_N: C35.2, J105.6 (RD-)
RJ_RD_P: C34.2, J105.3 (RD+)
RJ_TX_CT: C36.1, J105.4 (TCT)

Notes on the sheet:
WIZnet RJ45 reference topology. HR911105A pin numbering differs from J1B1211CCD. 100-ohm differential MDI routing; crystal load caps need final frequency measurement.
